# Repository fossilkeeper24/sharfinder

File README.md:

# sharfinder

 > followed pathfinder project from hack club [pathfinder.hackclub.com](https://pathfinder.hackclub.com/)

## PCB

### 3D

### 2D

## Description
3 lights and 3 buttons

So far, depending on which buttons are pressed and how quickly in succession, the lights should light up differently.

> I'll probably add an actual little minigame kinda thing later,  when I don't have a super tight schedule

## What did I learn?

I learnt how to make a github repo and update it whenever I make changes.

I have also learnt a bit of arduino syntax.
> the semi colons despise me

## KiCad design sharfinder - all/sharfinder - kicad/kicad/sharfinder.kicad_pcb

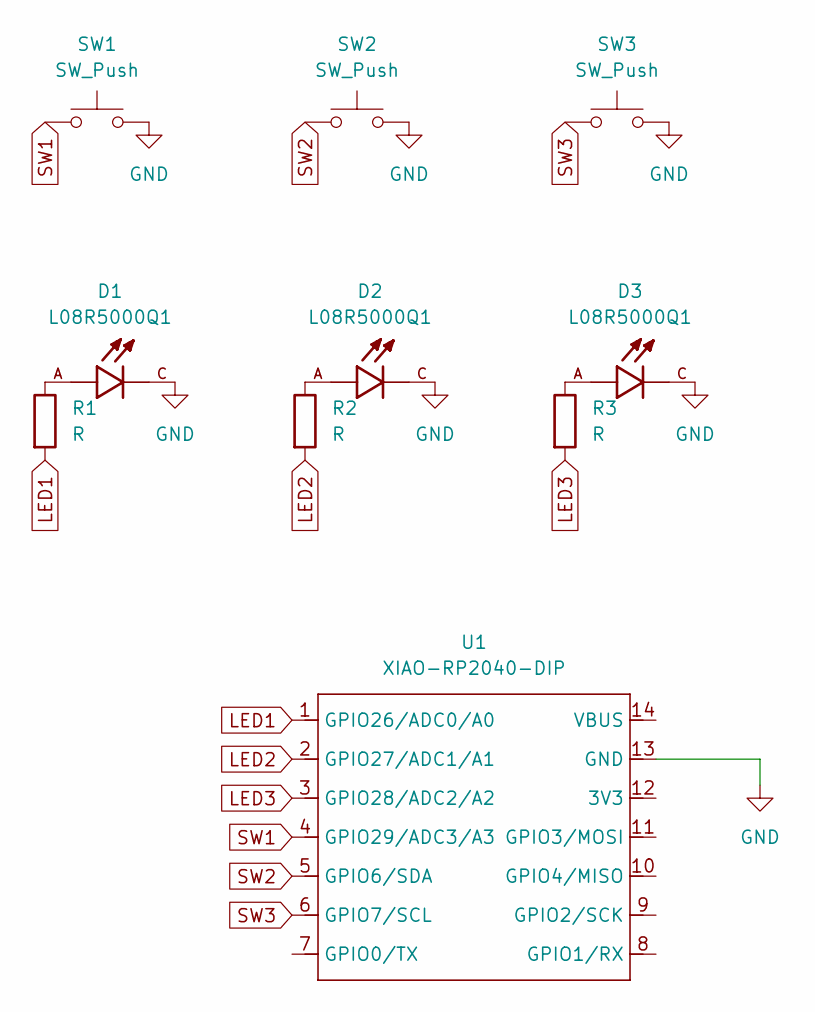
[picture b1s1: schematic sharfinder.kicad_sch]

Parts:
D1, D2, D3: L08R5000Q1; LEDRD254W57D500H1070; PARTREV NA
R1, R2, R3: R; R_Axial_DIN0204_L3.6mm_D1.6mm_P5.08mm_Horizontal
SW1, SW2, SW3: SW_Push; SW_Cherry_MX_1.00u_PCB
U1: XIAO-RP2040-DIP

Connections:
GND: D1.C, D2.C, D3.C, SW1.2, SW2.2, SW3.2, U1.13 (GND)
LED1: R1.2, U1.1 (GPIO26/ADC0/A0)
LED2: R2.2, U1.2 (GPIO27/ADC1/A1)
LED3: R3.2, U1.3 (GPIO28/ADC2/A2)
unnamed: D1.A, R1.1
unnamed: D2.A, R2.1
unnamed: D3.A, R3.1
SW1: SW1.1, U1.4 (GPIO29/ADC3/A3)
SW2: SW2.1, U1.5 (GPIO6/SDA)
SW3: SW3.1, U1.6 (GPIO7/SCL)

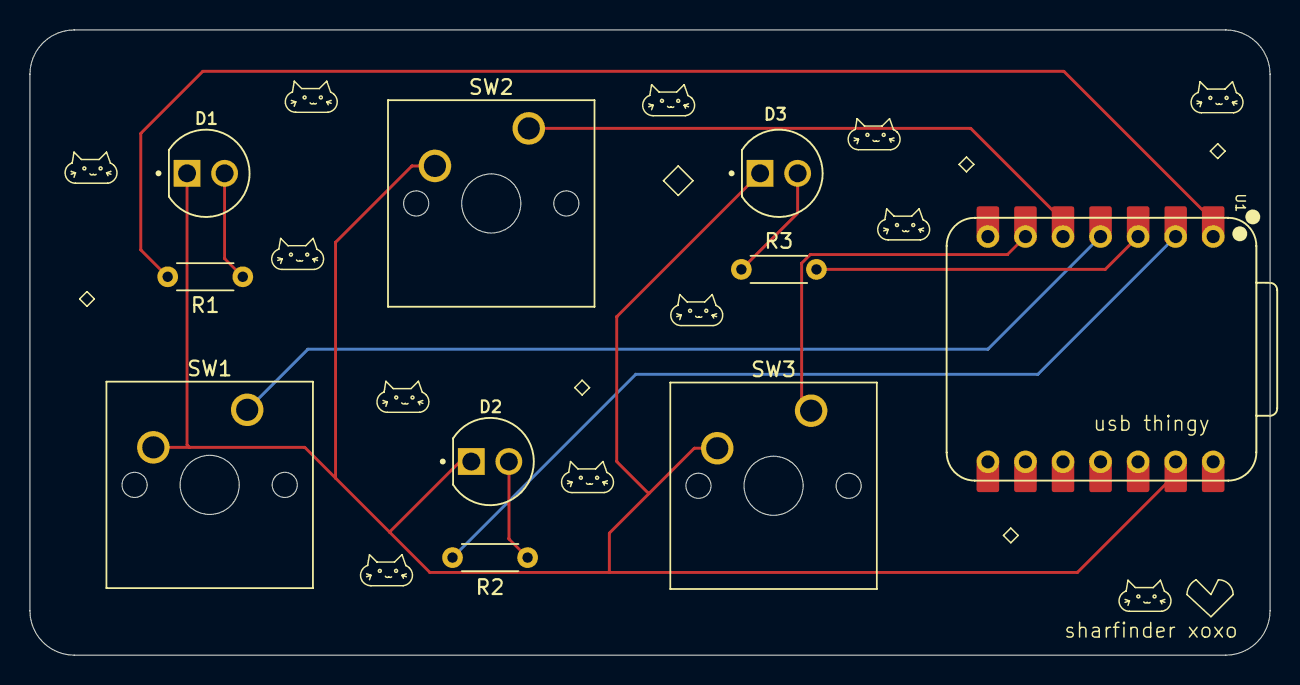
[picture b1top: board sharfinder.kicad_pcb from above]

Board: 2 copper layers, 83.9 x 42.3 mm, 10 parts (0 on the bottom side), 10 nets.

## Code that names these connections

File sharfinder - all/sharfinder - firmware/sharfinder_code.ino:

int BUT1 = D4;
int BUT2 = D5;
int BUT3 = D6;

int LED1 = D1;
int LED2 = D2;
int LED3 = D3;


void setup() {
  // put your setup code here, to run once:
  pinMode(BUT1, INPUT);
  pinMode(BUT2, INPUT);
  pinMode(BUT3, INPUT);

  pinMode(LED1, OUTPUT);
  pinMode(LED2, OUTPUT);
  pinMode(LED3, OUTPUT);

  long startTime = millis();


}

void loop() {
  // put your main code here, to run repeatedly:
  long but1time;
  long but2time;
  long but3time;
  
  if (digitalRead(BUT1) == HIGH) {
    but1time = millisec();
    digitalWrite(LED1, HIGH);
  } else {
    digitalWrite(LED1, LOW);
  }

  if (digitalRead(BUT2) == HIGH) {
    but2time = millisec();
    digitalWrite(LED2, HIGH);
  } else {
    digitalWrite(LED2, LOW);
  }

  if (digitalRead(BUT3) == HIGH) {
    digitalWrite(LED3, HIGH);
    but3time++;
  } else {
    digitalWrite(LED3, LOW);
  }

}

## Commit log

2025-07-01 added the first line
2025-07-02 uploaded kicad files
2025-07-02 re-added kicad files and added firmware
2025-07-02 added 3d models of components to pcb
2025-07-02 added image of PCB
2025-07-02 trying to see if my images are seen in md
2025-07-02 changed pcb image size
2025-07-02 added some minor details to pcb silkscreen
2025-07-02 added light blinking to firmware
2025-07-02 added more to the README
2025-07-02 added back of 3d PCB CAD model to README
2025-07-02 added schematic screenshot into imgs folder
    also changed one of the comments in firmware code
2025-07-02 gerber and drl files added for pcb
2025-07-02 something about prl
    i dont know what it means but sure
2025-07-04 made firmware all into one file
    it wouldn't work otherwise
2025-07-07 renamed folder and made a zip file for prod
2025-11-11 Cleaned up firmware a lil
    long pending commit but also added some code to help troubleshooting
2026-02-14 made a version that uses serial to communicate instead of leds
